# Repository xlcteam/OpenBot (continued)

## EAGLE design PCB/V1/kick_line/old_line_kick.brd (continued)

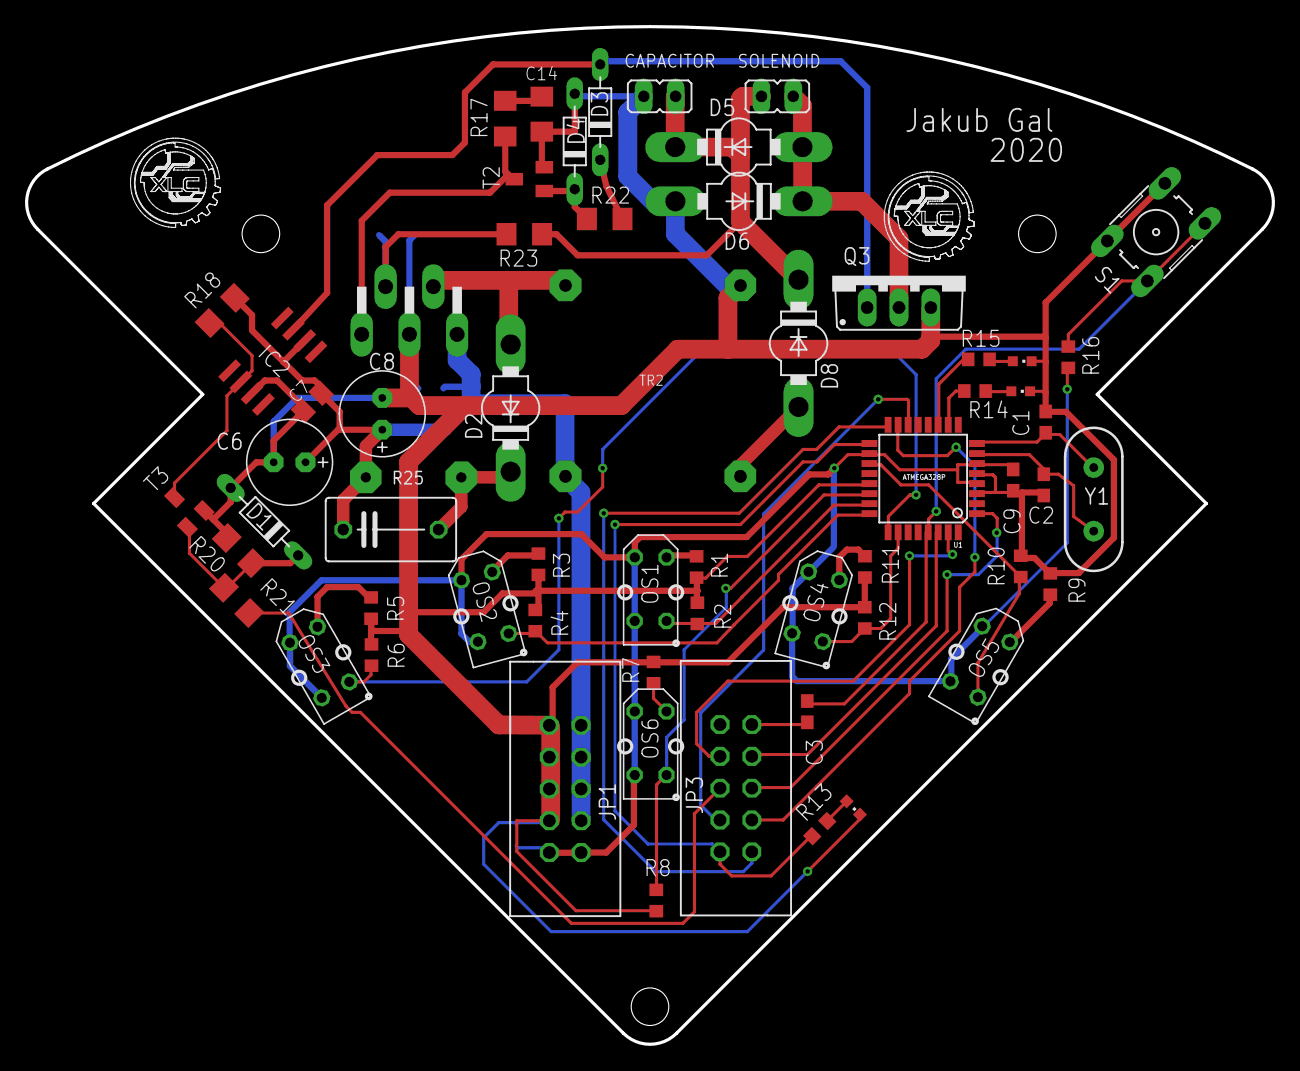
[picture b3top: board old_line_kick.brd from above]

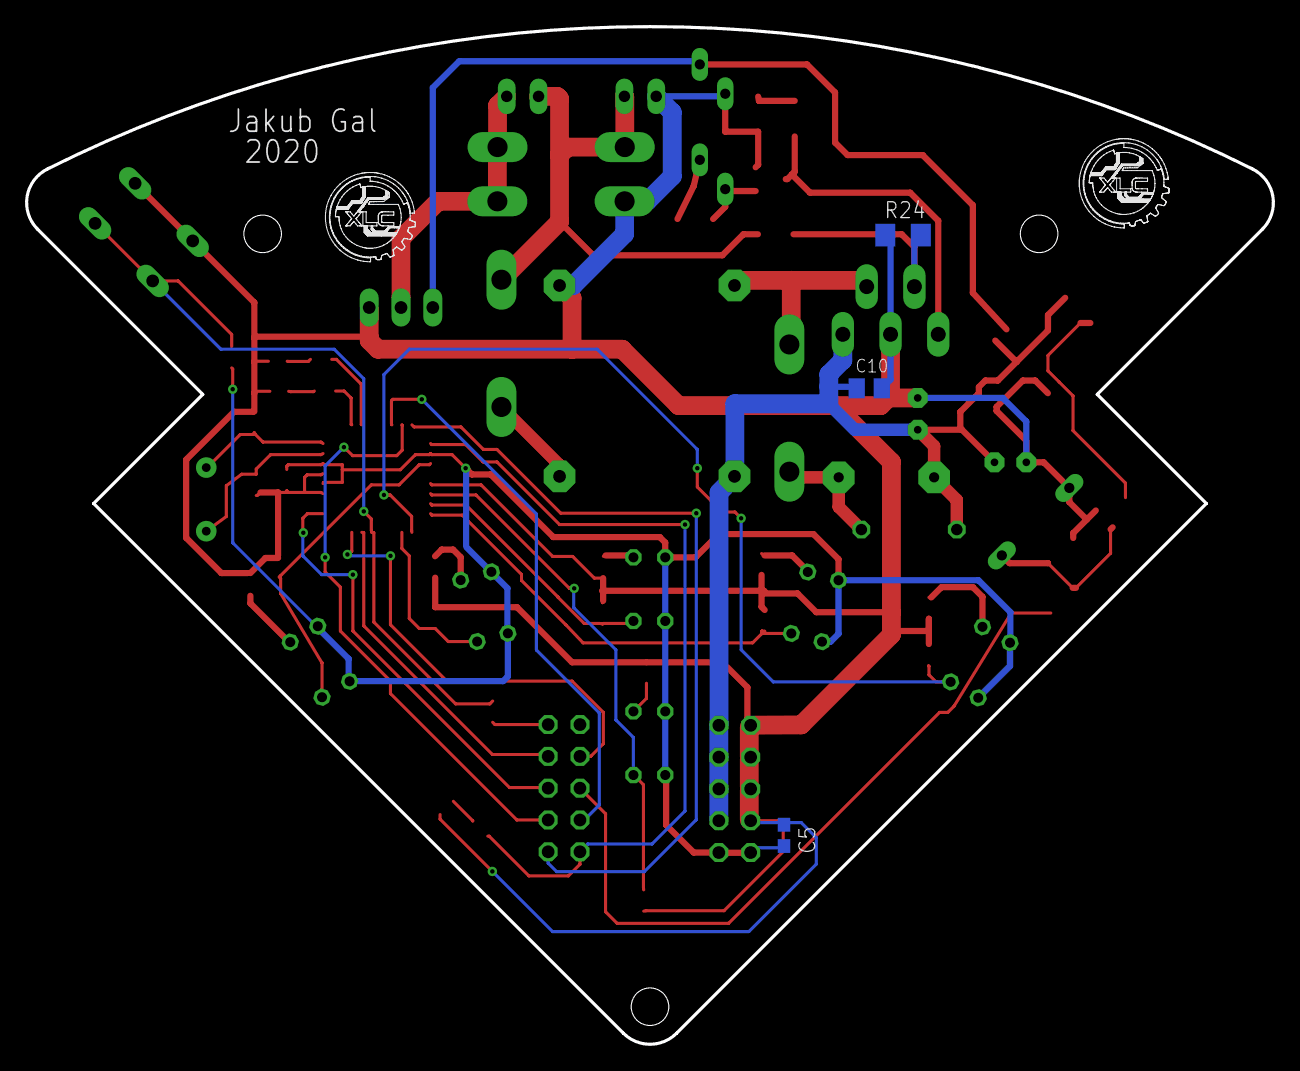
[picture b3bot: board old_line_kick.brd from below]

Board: 2 copper layers, 99.5 x 81.3 mm, 64 parts (3 on the bottom side), 45 nets.

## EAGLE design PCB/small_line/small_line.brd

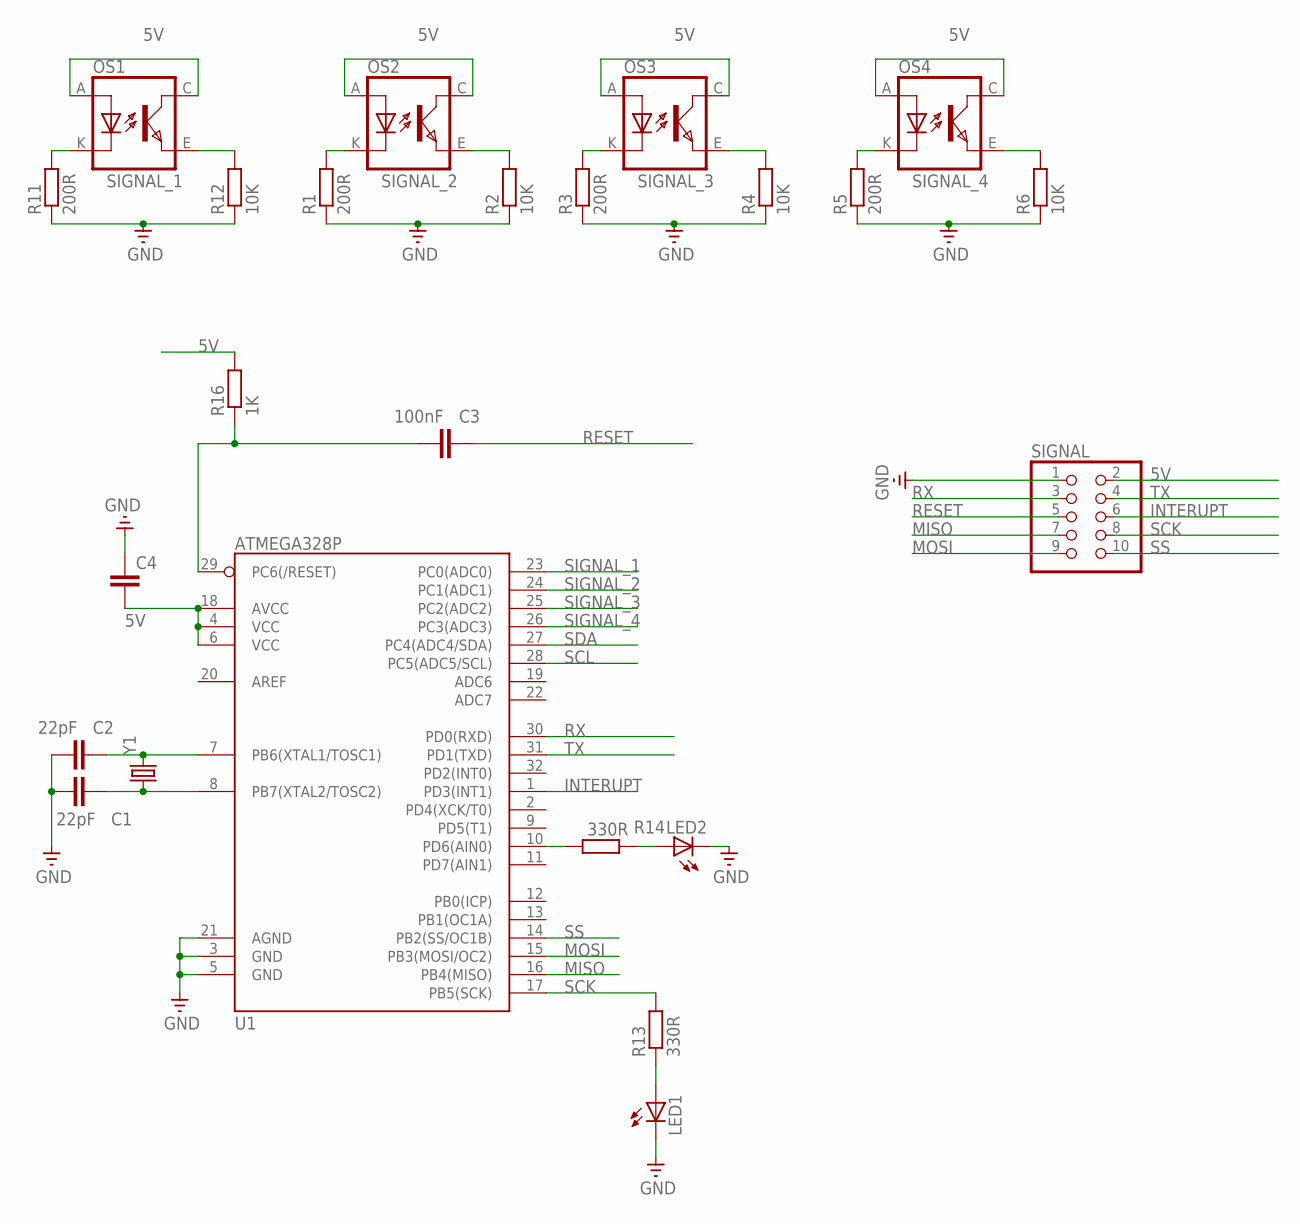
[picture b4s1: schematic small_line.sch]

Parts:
C1, C2: 22pF; C0603
C3: 100nF; C0603
C4: C-EUC0603; C0603
LED1, LED2: LEDCHIPLED_0603; CHIPLED_0603
OS1, OS2, OS3, OS4: TCRT5000
R1, R3, R5, R11: 200R; R0603
R2, R4, R6, R12: 10K; R0603
R13, R14: 330R; R0603
R16: 1K; R0603
SIGNAL: PINHD-2X5IDC; 2X05_IDC
U1: ATMEGA328P; TQFP32-08
Y1: CRYSTALHC49US; HC49US

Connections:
5V: C4.2, OS1.A (ANODE), OS1.C (COLLECTOR), OS2.A (ANODE), OS2.C (COLLECTOR), OS3.A (ANODE), OS3.C (COLLECTOR), OS4.A (ANODE), OS4.C (COLLECTOR), R16.2, SIGNAL.2, U1.4 (VCC), U1.6 (VCC), U1.18 (AVCC)
GND: C1.1, C2.1, C4.1, LED1.C, LED2.C, R1.1, R2.1, R3.1, R4.1, R5.1, R6.1, R11.1, R12.1, SIGNAL.1, U1.3 (GND), U1.5 (GND), U1.21 (AGND)
INTERUPT: SIGNAL.6, U1.1 (PD3(INT1))
MISO: SIGNAL.7, U1.16 (PB4(MISO))
MOSI: SIGNAL.9, U1.15 (PB3(MOSI/OC2))
unnamed: OS2.K (CATHODE), R1.2
unnamed: OS3.K (CATHODE), R3.2
unnamed: OS4.K (CATHODE), R5.2
unnamed: OS1.K (CATHODE), R11.2
unnamed: C2.2, U1.7 (PB6(XTAL1/TOSC1)), Y1.2
unnamed: C1.2, U1.8 (PB7(XTAL2/TOSC2)), Y1.1
unnamed: C3.1, R16.1, U1.29 (PC6(/RESET))
unnamed: LED1.A, R13.1
unnamed: LED2.A, R14.1
unnamed: R14.2, U1.10 (PD6(AIN0))
RESET: C3.2, SIGNAL.5
RX: SIGNAL.3, U1.30 (PD0(RXD))
SCK: R13.2, SIGNAL.8, U1.17 (PB5(SCK))
SCL: U1.28 (PC5(ADC5/SCL))
SDA: U1.27 (PC4(ADC4/SDA))
SIGNAL_1: OS1.E (EMITTER), R12.2, U1.23 (PC0(ADC0))
SIGNAL_2: OS2.E (EMITTER), R2.2, U1.24 (PC1(ADC1))
SIGNAL_3: OS3.E (EMITTER), R4.2, U1.25 (PC2(ADC2))
SIGNAL_4: OS4.E (EMITTER), R6.2, U1.26 (PC3(ADC3))
SS: SIGNAL.10, U1.14 (PB2(SS/OC1B))
TX: SIGNAL.4, U1.31 (PD1(TXD))

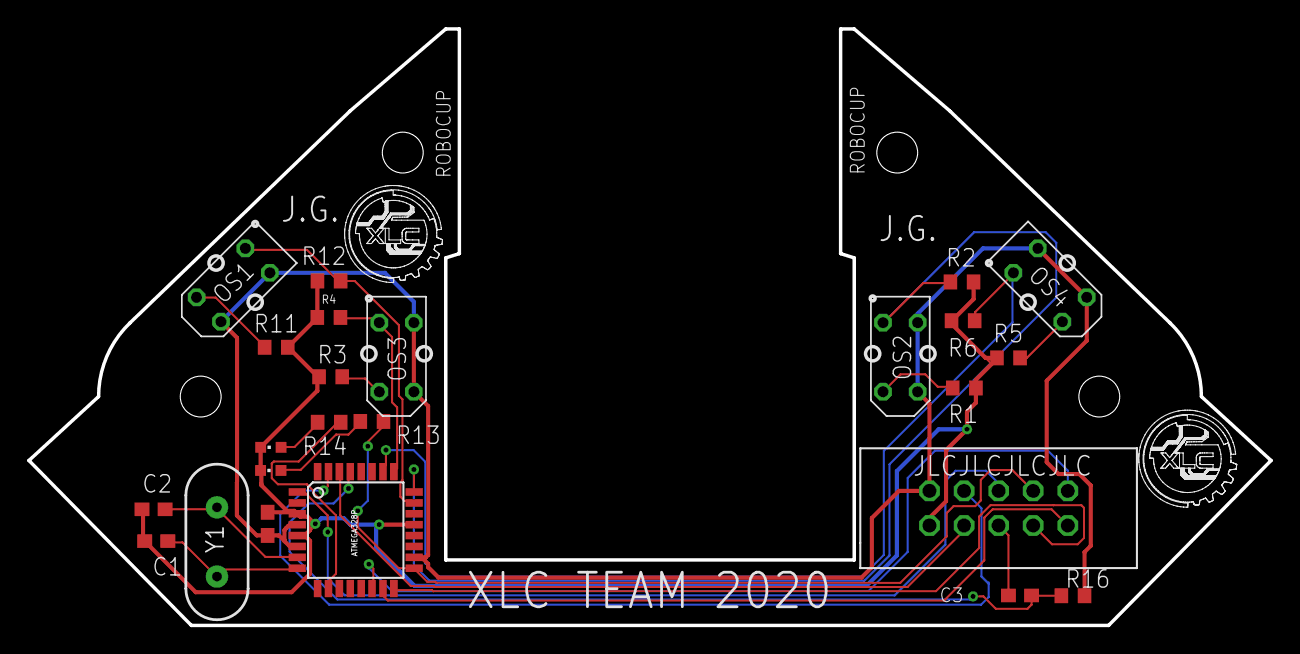
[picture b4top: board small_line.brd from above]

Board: 2 copper layers, 91.2 x 43.8 mm, 24 parts (0 on the bottom side), 24 nets.

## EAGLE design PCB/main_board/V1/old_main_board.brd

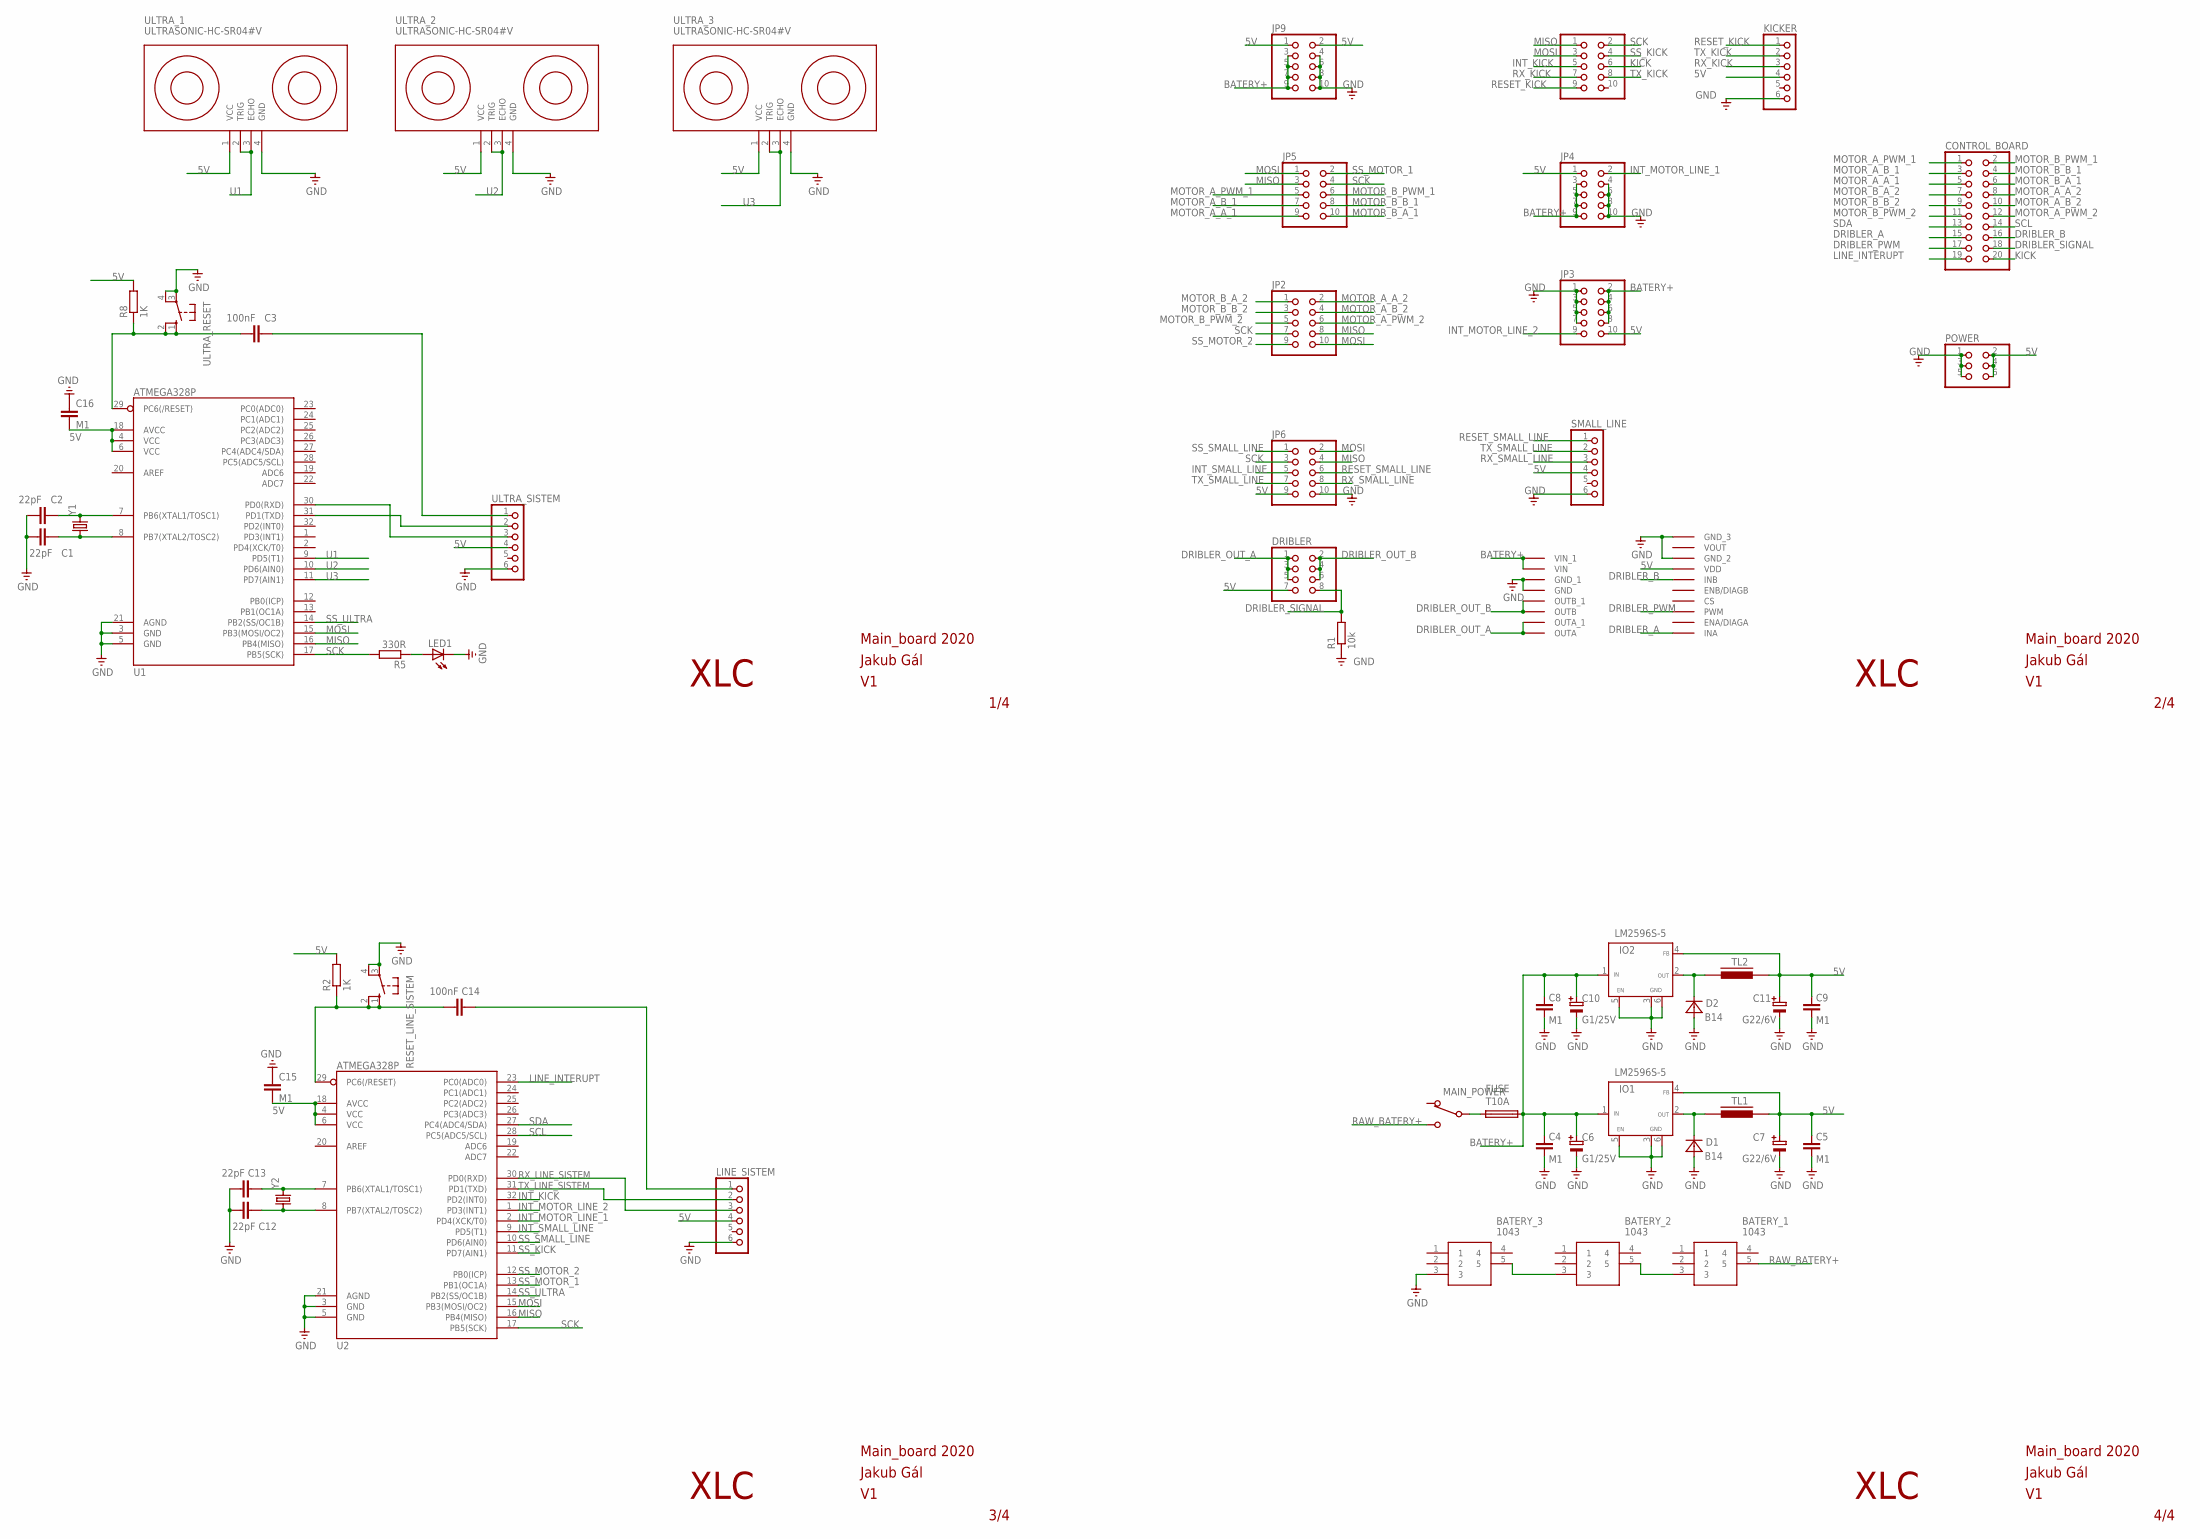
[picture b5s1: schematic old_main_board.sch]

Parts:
BATERY_1, BATERY_2, BATERY_3: 1043
C1, C2, C12, C13: 22pF; C0603
C3, C14: 100nF; C0603
C4, C5, C8, C9: M1; SMD-1206
C6, C10: G1/25V; SMD-ELE-D
C7, C11: G22/6V; SMD-ELE-D
C15, C16: M1; C0603
CONTROL_BOARD: PINHD-2X10_2.54-SMD; 2X10SMD
D1, D2: B14; D-3,6X5,5
DRIBLER: PINHD-2X4_2.54-SMD; 2X04SMD
FUSE: T10A; SH22,5A
IO1, IO2: LM2596S-5; TO263-5
JP2, JP3, JP4, JP5, JP6, JP8, JP9: PINHD-2X5_2.54-SMD; 2X05SMD
KICKER: PINHD-1X6; 1X06
LED1: LEDCHIPLED_0603; CHIPLED_0603
LINE_SISTEM: PINHD-1X6; 1X06
MAIN_POWER: PREP-1PB; P-B069B
POWER: PINHD-2X3_2.54-SMD; 2X03SMD
R1: 10k; R0603
R2, R8: 1K; R0603
R5: 330R; R0603
RESET_LINE_SISTEM: 10-XX; B3F-10XX
SMALL_LINE: PINHD-1X6; 1X06
TL1, TL2: INDUK-TLSMD1; INDUK-TL
U1, U2: ATMEGA328P; TQFP32-08
U$4: MOTOR_DRIVER
ULTRA_1, ULTRA_2, ULTRA_3: ULTRASONIC-HC-SR04#V
ULTRA_RESET: 10-XX; B3F-10XX
ULTRA_SISTEM: PINHD-1X6; 1X06
Y1, Y2: CRYSTALHC49US; HC49US

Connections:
5V: C5.2, C7.PLUS, C9.2, C11.PLUS, C15.2, C16.2, DRIBLER.7, IO1.4 (FB), IO2.4 (FB), JP3.10, JP4.1, JP6.9, JP9.1, JP9.2, KICKER.4, LINE_SISTEM.4, POWER.2, POWER.4, POWER.6, R2.2, R8.2, SMALL_LINE.4, TL1.2, TL2.2, U1.4 (VCC), U1.6 (VCC), U1.18 (AVCC), U2.4 (VCC), U2.6 (VCC), U2.18 (AVCC), U$4.VDD, ULTRA_1.1 (VCC), ULTRA_2.1 (VCC), ULTRA_3.1 (VCC), ULTRA_SISTEM.4
BATERY+: C4.2, C6.PLUS, C8.2, C10.PLUS, FUSE.2, IO1.1 (IN), IO2.1 (IN), JP3.2, JP3.4, JP3.6, JP3.8, JP4.3, JP4.5, JP4.7, JP4.9, JP9.3, JP9.5, JP9.7, JP9.9, U$4.VIN, U$4.VIN_1
DRIBLER_A: CONTROL_BOARD.15, U$4.INA
DRIBLER_B: CONTROL_BOARD.16, U$4.INB
DRIBLER_OUT_A: DRIBLER.1, DRIBLER.3, DRIBLER.5, U$4.OUTA, U$4.OUTA_1
DRIBLER_OUT_B: DRIBLER.2, DRIBLER.4, DRIBLER.6, U$4.OUTB, U$4.OUTB_1
DRIBLER_PWM: CONTROL_BOARD.17, U$4.PWM
DRIBLER_SIGNAL: CONTROL_BOARD.18, DRIBLER.8, R1.2
GND: BATERY_3.3, C1.1, C2.1, C4.1, C5.1, C6.MINUS, C7.MINUS, C8.1, C9.1, C10.MINUS, C11.MINUS, C12.1, C13.1, C15.1, C16.1, D1.A, D2.A, IO1.3 (GND), IO1.5 (EN), IO1.6 (GND), IO2.3 (GND), IO2.5 (EN), IO2.6 (GND), JP3.1, JP3.3, JP3.5, JP3.7, JP4.4, JP4.6, JP4.8, JP4.10, JP6.10, JP9.4, JP9.6, JP9.8, JP9.10, KICKER.6, LED1.C, LINE_SISTEM.6, POWER.1, POWER.3, POWER.5, R1.1, RESET_LINE_SISTEM.3, RESET_LINE_SISTEM.4 (P1), SMALL_LINE.6, U1.3 (GND), U1.5 (GND), U1.21 (AGND), U2.3 (GND), U2.5 (GND), U2.21 (AGND), U$4.GND, U$4.GND_1, U$4.GND_2, U$4.GND_3, ULTRA_1.4 (GND), ULTRA_2.4 (GND), ULTRA_3.4 (GND), ULTRA_RESET.3, ULTRA_RESET.4 (P1), ULTRA_SISTEM.6
INT_KICK: JP8.5, U2.32 (PD2(INT0))
INT_MOTOR_LINE_1: JP4.2, U2.2 (PD4(XCK/T0))
INT_MOTOR_LINE_2: JP3.9, U2.1 (PD3(INT1))
INT_SMALL_LINE: JP6.5, U2.9 (PD5(T1))
KICK: CONTROL_BOARD.20, JP8.6
LINE_INTERUPT: CONTROL_BOARD.19, U2.23 (PC0(ADC0))
MISO: JP2.8, JP5.3, JP6.4, JP8.1, U1.16 (PB4(MISO)), U2.16 (PB4(MISO))
MOSI: JP2.10, JP5.1, JP6.2, JP8.3, U1.15 (PB3(MOSI/OC2)), U2.15 (PB3(MOSI/OC2))
MOTOR_A_A_1: CONTROL_BOARD.5, JP5.9
MOTOR_A_A_2: CONTROL_BOARD.8, JP2.2
MOTOR_A_B_1: CONTROL_BOARD.3, JP5.7
MOTOR_A_B_2: CONTROL_BOARD.10, JP2.4
MOTOR_A_PWM_1: CONTROL_BOARD.1, JP5.5
MOTOR_A_PWM_2: CONTROL_BOARD.12, JP2.6
MOTOR_B_A_1: CONTROL_BOARD.6, JP5.10
MOTOR_B_A_2: CONTROL_BOARD.7, JP2.1
MOTOR_B_B_1: CONTROL_BOARD.4, JP5.8
MOTOR_B_B_2: CONTROL_BOARD.9, JP2.3
MOTOR_B_PWM_1: CONTROL_BOARD.2, JP5.6
MOTOR_B_PWM_2: CONTROL_BOARD.11, JP2.5
unnamed: BATERY_1.3, BATERY_2.5
unnamed: BATERY_2.3, BATERY_3.5
unnamed: D2.K, IO2.2 (OUT), TL2.1
unnamed: FUSE.1, MAIN_POWER.2 (2-COM)
unnamed: C13.2, U2.7 (PB6(XTAL1/TOSC1)), Y2.2
unnamed: D1.K, IO1.2 (OUT), TL1.1
unnamed: C2.2, U1.7 (PB6(XTAL1/TOSC1)), Y1.2
unnamed: C1.2, U1.8 (PB7(XTAL2/TOSC2)), Y1.1
unnamed: C12.2, U2.8 (PB7(XTAL2/TOSC2)), Y2.1
unnamed: C14.2, LINE_SISTEM.1
unnamed: C14.1, R2.1, RESET_LINE_SISTEM.1 (S), RESET_LINE_SISTEM.2 (S1), U2.29 (PC6(/RESET))
unnamed: U1.30 (PD0(RXD)), ULTRA_SISTEM.3
unnamed: U1.31 (PD1(TXD)), ULTRA_SISTEM.2
unnamed: C3.2, ULTRA_SISTEM.1
unnamed: C3.1, R8.1, U1.29 (PC6(/RESET)), ULTRA_RESET.1 (S), ULTRA_RESET.2 (S1)
unnamed: LED1.A, R5.1
RAW_BATERY+: BATERY_1.5, MAIN_POWER.1 (1-OFF)
RESET_KICK: JP8.9, KICKER.1
RESET_SMALL_LINE: JP6.6, SMALL_LINE.1
RX_KICK: JP8.7, KICKER.3
RX_LINE_SISTEM: LINE_SISTEM.3, U2.30 (PD0(RXD))
RX_SMALL_LINE: JP6.8, SMALL_LINE.3
SCK: JP2.7, JP5.4, JP6.3, JP8.2, R5.2, U1.17 (PB5(SCK)), U2.17 (PB5(SCK))
SCL: CONTROL_BOARD.14, U2.28 (PC5(ADC5/SCL))
SDA: CONTROL_BOARD.13, U2.27 (PC4(ADC4/SDA))
SS_KICK: JP8.4, U2.11 (PD7(AIN1))
SS_MOTOR_1: JP5.2, U2.13 (PB1(OC1A))
SS_MOTOR_2: JP2.9, U2.12 (PB0(ICP))
SS_SMALL_LINE: JP6.1, U2.10 (PD6(AIN0))
SS_ULTRA: U1.14 (PB2(SS/OC1B)), U2.14 (PB2(SS/OC1B))
TX_KICK: JP8.8, KICKER.2
TX_LINE_SISTEM: LINE_SISTEM.2, U2.31 (PD1(TXD))
TX_SMALL_LINE: JP6.7, SMALL_LINE.2
U1: U1.9 (PD5(T1)), ULTRA_1.2 (TRIG), ULTRA_1.3 (ECHO)
U2: U1.10 (PD6(AIN0)), ULTRA_2.2 (TRIG), ULTRA_2.3 (ECHO)
U3: U1.11 (PD7(AIN1)), ULTRA_3.2 (TRIG), ULTRA_3.3 (ECHO)

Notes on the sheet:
1/4
2/4
3/4
4/4
XLC
Main_board 2020
Jakub Gál

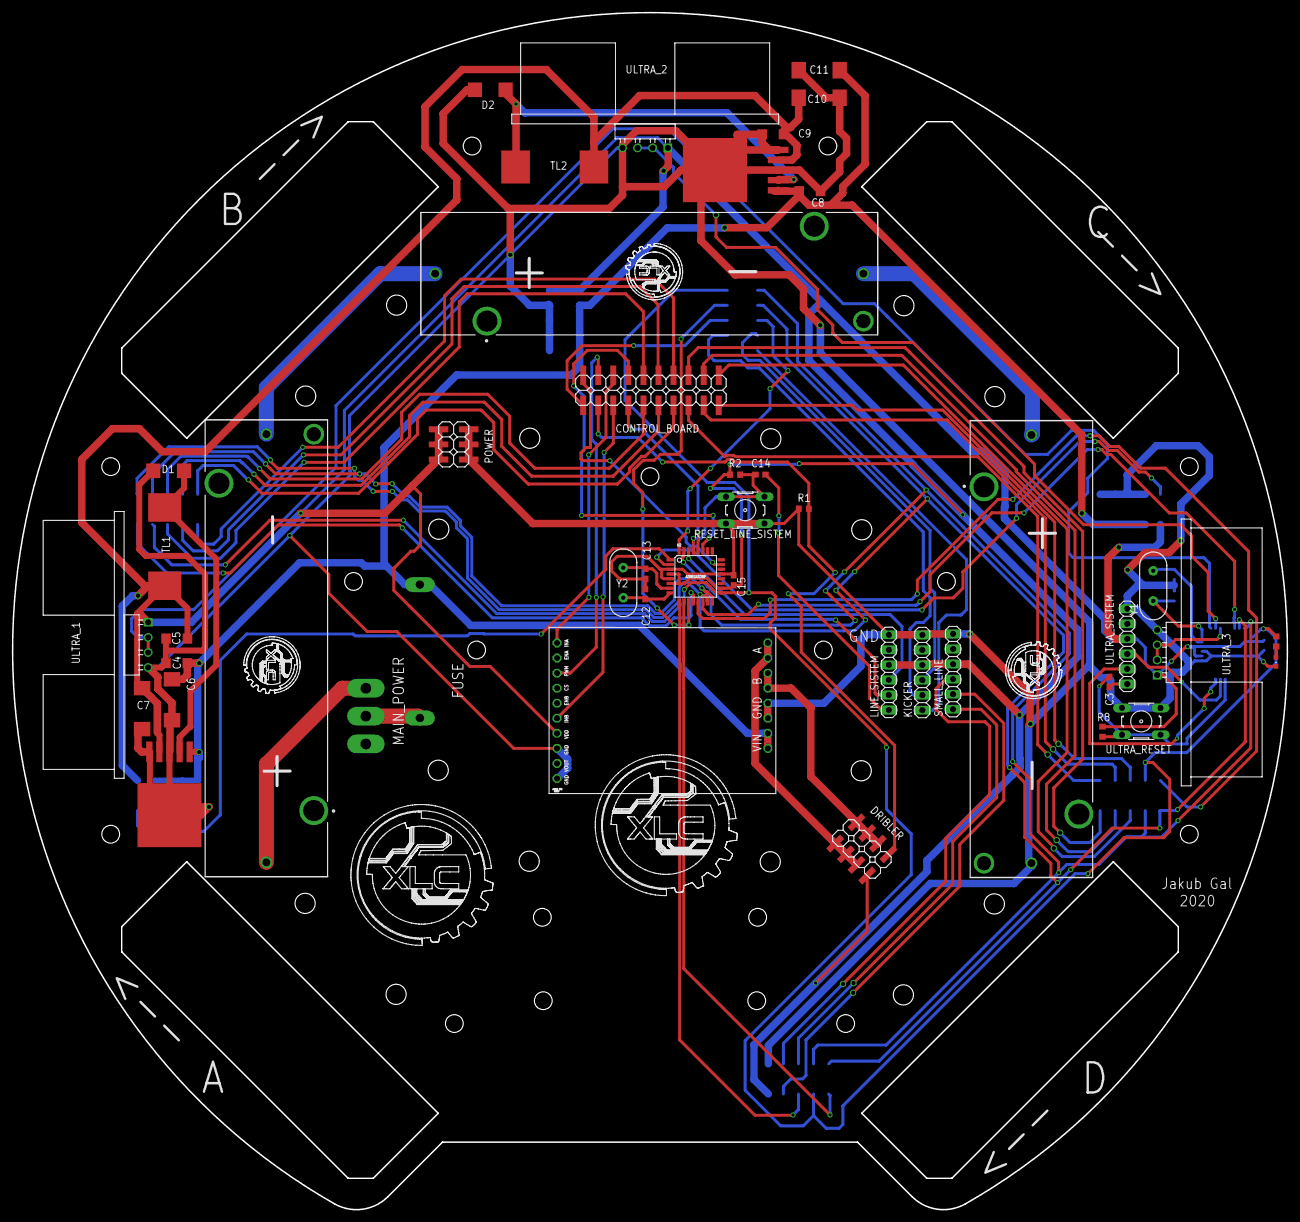
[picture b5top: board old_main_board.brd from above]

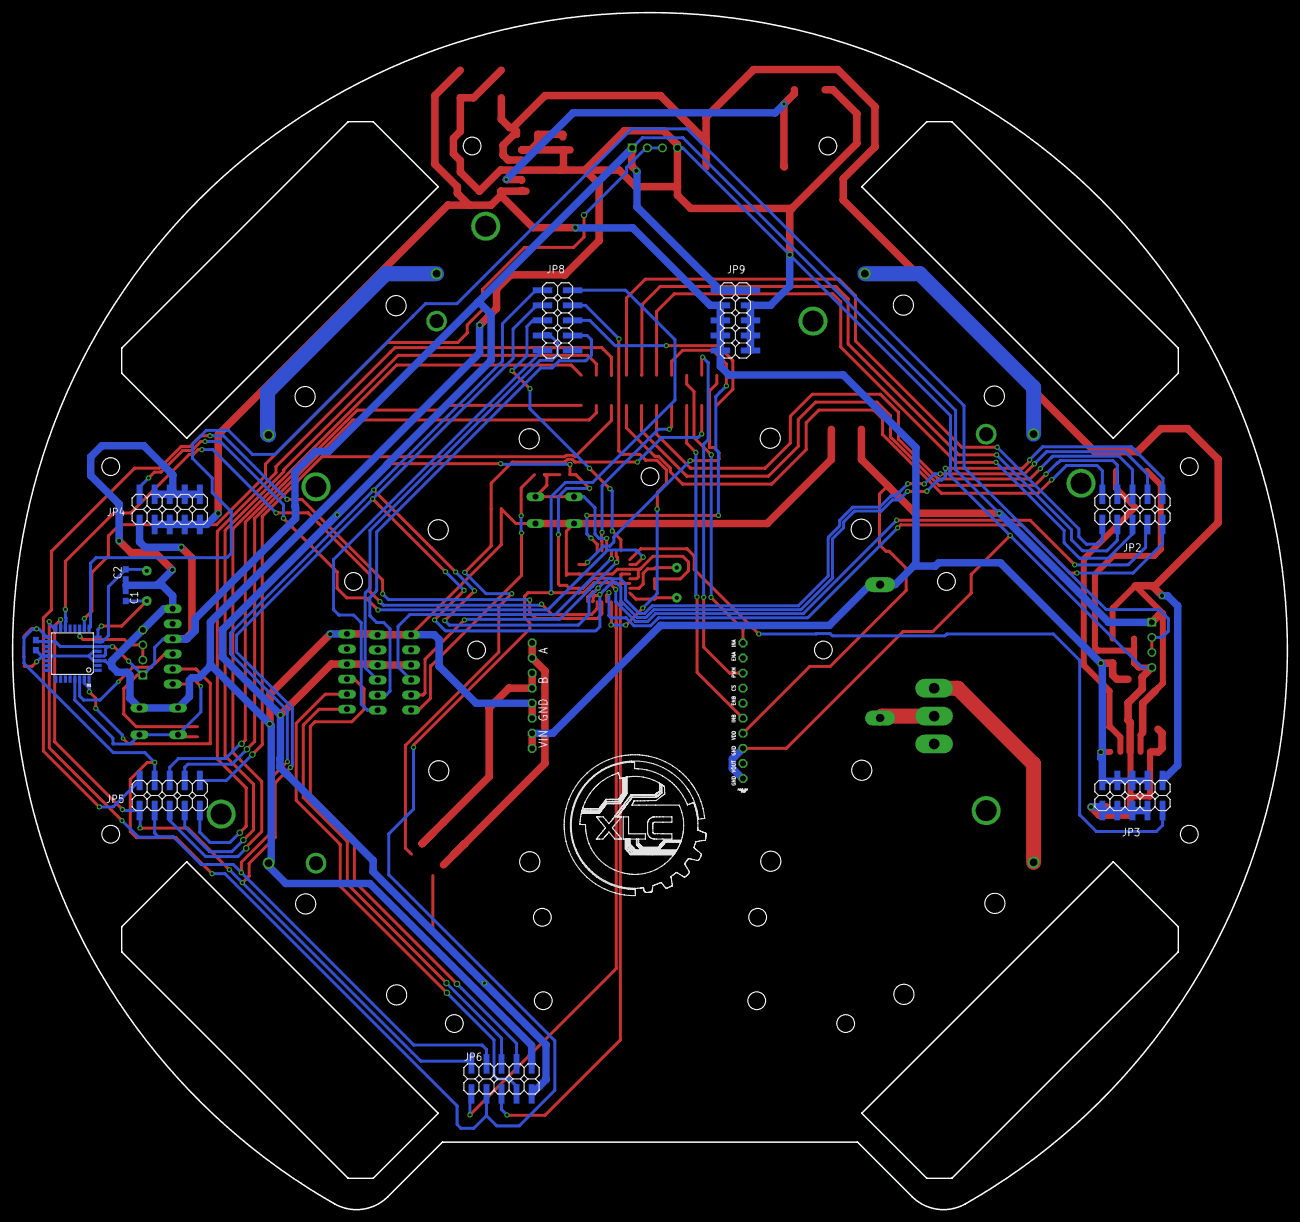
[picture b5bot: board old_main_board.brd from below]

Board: 2 copper layers, 215.0 x 201.9 mm, 56 parts (11 on the bottom side), 65 nets.

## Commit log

2020-03-01 initial
    New Robocup 2020 Open robot
2020-03-01 Edit README
2020-03-06 first_steps
    First working program
    + rpi camera procesing
    + movements
2020-03-07 Clean + strategy
2020-03-09 Menu
2020-03-19 Dribler+kicker
2020-03-23 testing
2020-04-01 Dataset for detection (2000 img)
2020-06-25 VirtualPoster
2021-04-21 documentation
2021-06-22 RCJ_2021_update
2021-06-22 readmi_update
